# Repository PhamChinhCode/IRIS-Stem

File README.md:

# Bộ kit giảng dạy STEM – ESP32-S3 + MicroBlocks

Hệ thống module tái sử dụng để dạy nhà thông minh, robot và IoT cho học sinh 12–18 tuổi, lập trình kéo thả trên MicroBlocks.

## Đọc từ đâu

| Muốn biết | Mở |
|---|---|
| Kit gồm những gì, 25 dự án dùng module nào | [docs/THIET-KE-HE-THONG.md](docs/THIET-KE-HE-THONG.md) |
| Xem trực quan: dự án, sơ đồ nối dây, mô hình 3D, sơ đồ mạch | [stem-kit-map/index.html](stem-kit-map/index.html) |
| Sơ đồ nguyên lý, linh kiện, mạch in của từng bo | [hardware/THIET-KE-MACH.md](hardware/THIET-KE-MACH.md) |
| Chi tiết một bo tự thiết kế: gán chân, linh kiện, bố trí, kiểm thử | `hardware/<bo>/THIET-KE-<mã>.md`, ví dụ [THIET-KE-C1.md](hardware/C1-bo-chu/THIET-KE-C1.md) (có cho C1, C2, S1, S2, S3) |
| Kích thước bo, chi tiết in 3D, vỏ hộp, mô hình lắp ráp | [docs/THIET-KE-CO-KHI.md](docs/THIET-KE-CO-KHI.md) |
| Cách đưa tệp 3D, hình mạch, PDF lên trang web | [stem-kit-map/HUONG-DAN.md](stem-kit-map/HUONG-DAN.md) |

## Cấu trúc thư mục

```
docs/           Tài liệu thiết kế, hình minh hoạ
stem-kit-map/   Trang bản đồ kit (web) và lệnh cập nhật update_3d.py
hardware/       Mạch KiCad; THIET-KE-MACH.md là tài liệu thiết kế mạch
  common/         Thư viện ký hiệu, chân linh kiện, mã dựng sơ đồ và mạch in dùng chung
  C1-bo-chu/      Bo chủ ESP32-S3 (64 × 48 mm)
  C2-nguon-pin/   Nguồn pin 2S
  S1-driver-dong-co/
  S2-do-line/
  S3-imu/
  O7-servo-16-kenh/
  bo-mang/        19 bo mang cho module đơn giản (I1–I14, O1–O5), mỗi bo một thư mục
firmware/       Firmware STM32G030 của module thông minh
  common/         Khung I2C và bootloader dùng chung
  S1-driver-dong-co/
  S2-do-line/
  S3-imu/
libraries/      Thư viện khối MicroBlocks tự viết
mechanical/     Cơ khí: mã CAD tham số (src/), tệp in 3D (STL/)
projects/       Chương trình mẫu và mô hình lắp ráp của 25 dự án, theo 5 cấp độ
curriculum/     Giáo án, phiếu bài học
```

`Iris blocks/` là bản fork MicroBlocks (phần mềm lập trình và firmware máy ảo, giấy phép MPL 2.0). Các thay đổi so với bản gốc ghi trong [Iris blocks/DOC-STNAPP.md](Iris%20blocks/DOC-STNAPP.md); bối cảnh ở mục 12 của tài liệu thiết kế.

## Tình trạng

| Phần | Đã có | Còn thiếu |
|---|---|---|
| Sơ đồ nguyên lý | Đủ 25 bo, ERC không lỗi | Mã LCSC cho phần lớn linh kiện; đối chiếu datasheet HY2120-CB và 8205A trên C2 |
| Mạch in | 19 bo mang đã đi dây | C1, C2, S1, S2, S3, O7; soát tay và xuất Gerber cho 19 bo mang |
| Vỏ in 3D | Đế và nắp cho 19 bo mang (I3, I13 chỉ có đế) | Vỏ cho 6 bo còn lại |
| Mô hình lắp ráp | 7 cụm dự án, không va chạm; cánh tay robot dùng servo MG90S | Mô hình riêng cho từng dự án |
| Trang bản đồ kit | 25 dự án, 25 module, mô hình 3D, hình mạch, tài liệu PDF | |

## Trang bản đồ kit

Trang lấy dữ liệu thẳng từ các thư mục thiết kế. Sau khi sửa mạch hoặc mô hình, chạy một lệnh trong `stem-kit-map/`:

```bash
python update_3d.py
```

Lệnh tìm tệp theo **tên**, nên chỉ cần lưu đúng chỗ và đúng tên:

| Nội dung trên trang | Tệp nguồn | Ví dụ |
|---|---|---|
| Mô hình 3D của module | `hardware/**/<mã>.step` | `hardware/C1-bo-chu/C1.step` |
| Mô hình 3D của dự án | `projects/**/Project<số>.step` | `projects/Project11.step` |
| Sơ đồ nguyên lý | `hardware/**/<mã>.kicad_sch` | `hardware/bo-mang/I1/I1.kicad_sch` |
| Hình mạch in | `hardware/**/<mã>.kicad_pcb` | `hardware/bo-mang/I1/I1.kicad_pcb` |
| Tài liệu PDF | `hardware/**/<mã>.pdf` | `hardware/bo-mang/I1/I1.pdf` |

Module và dự án chưa có tệp riêng thì dùng mô hình dựng từ mã trong `mechanical/src`. Xuất hình mạch cần KiCad 10; đọc tệp STEP cần `cadgen` (xem hướng dẫn).

## Quy ước

- Mã module (C1, S1, I6, O3...) theo mục 4 của tài liệu thiết kế, dùng làm tiền tố tên thư mục và tên tệp.
- Mỗi module tự thiết kế có thư mục cùng tên ở `hardware/` và `firmware/`.
- Tệp trong `mechanical/STEP/` dựng lại được từ mã nên không đưa vào git. Riêng mô hình servo MG90S tải từ step.parts nằm ở `mechanical/STEP/mua_san/`, phải tải lại trên máy mới (tìm «Adafruit 1143» trên step.parts, lưu thành `adafruit_1143_micro_servo_high_torque_metal_gear.step`).
- Các lệnh sinh sơ đồ và mạch in (`ve_so_do.py`, `ve_pcb.py`) **ghi đè** tệp KiCad. Không chạy lại cho bo đã sửa tay.

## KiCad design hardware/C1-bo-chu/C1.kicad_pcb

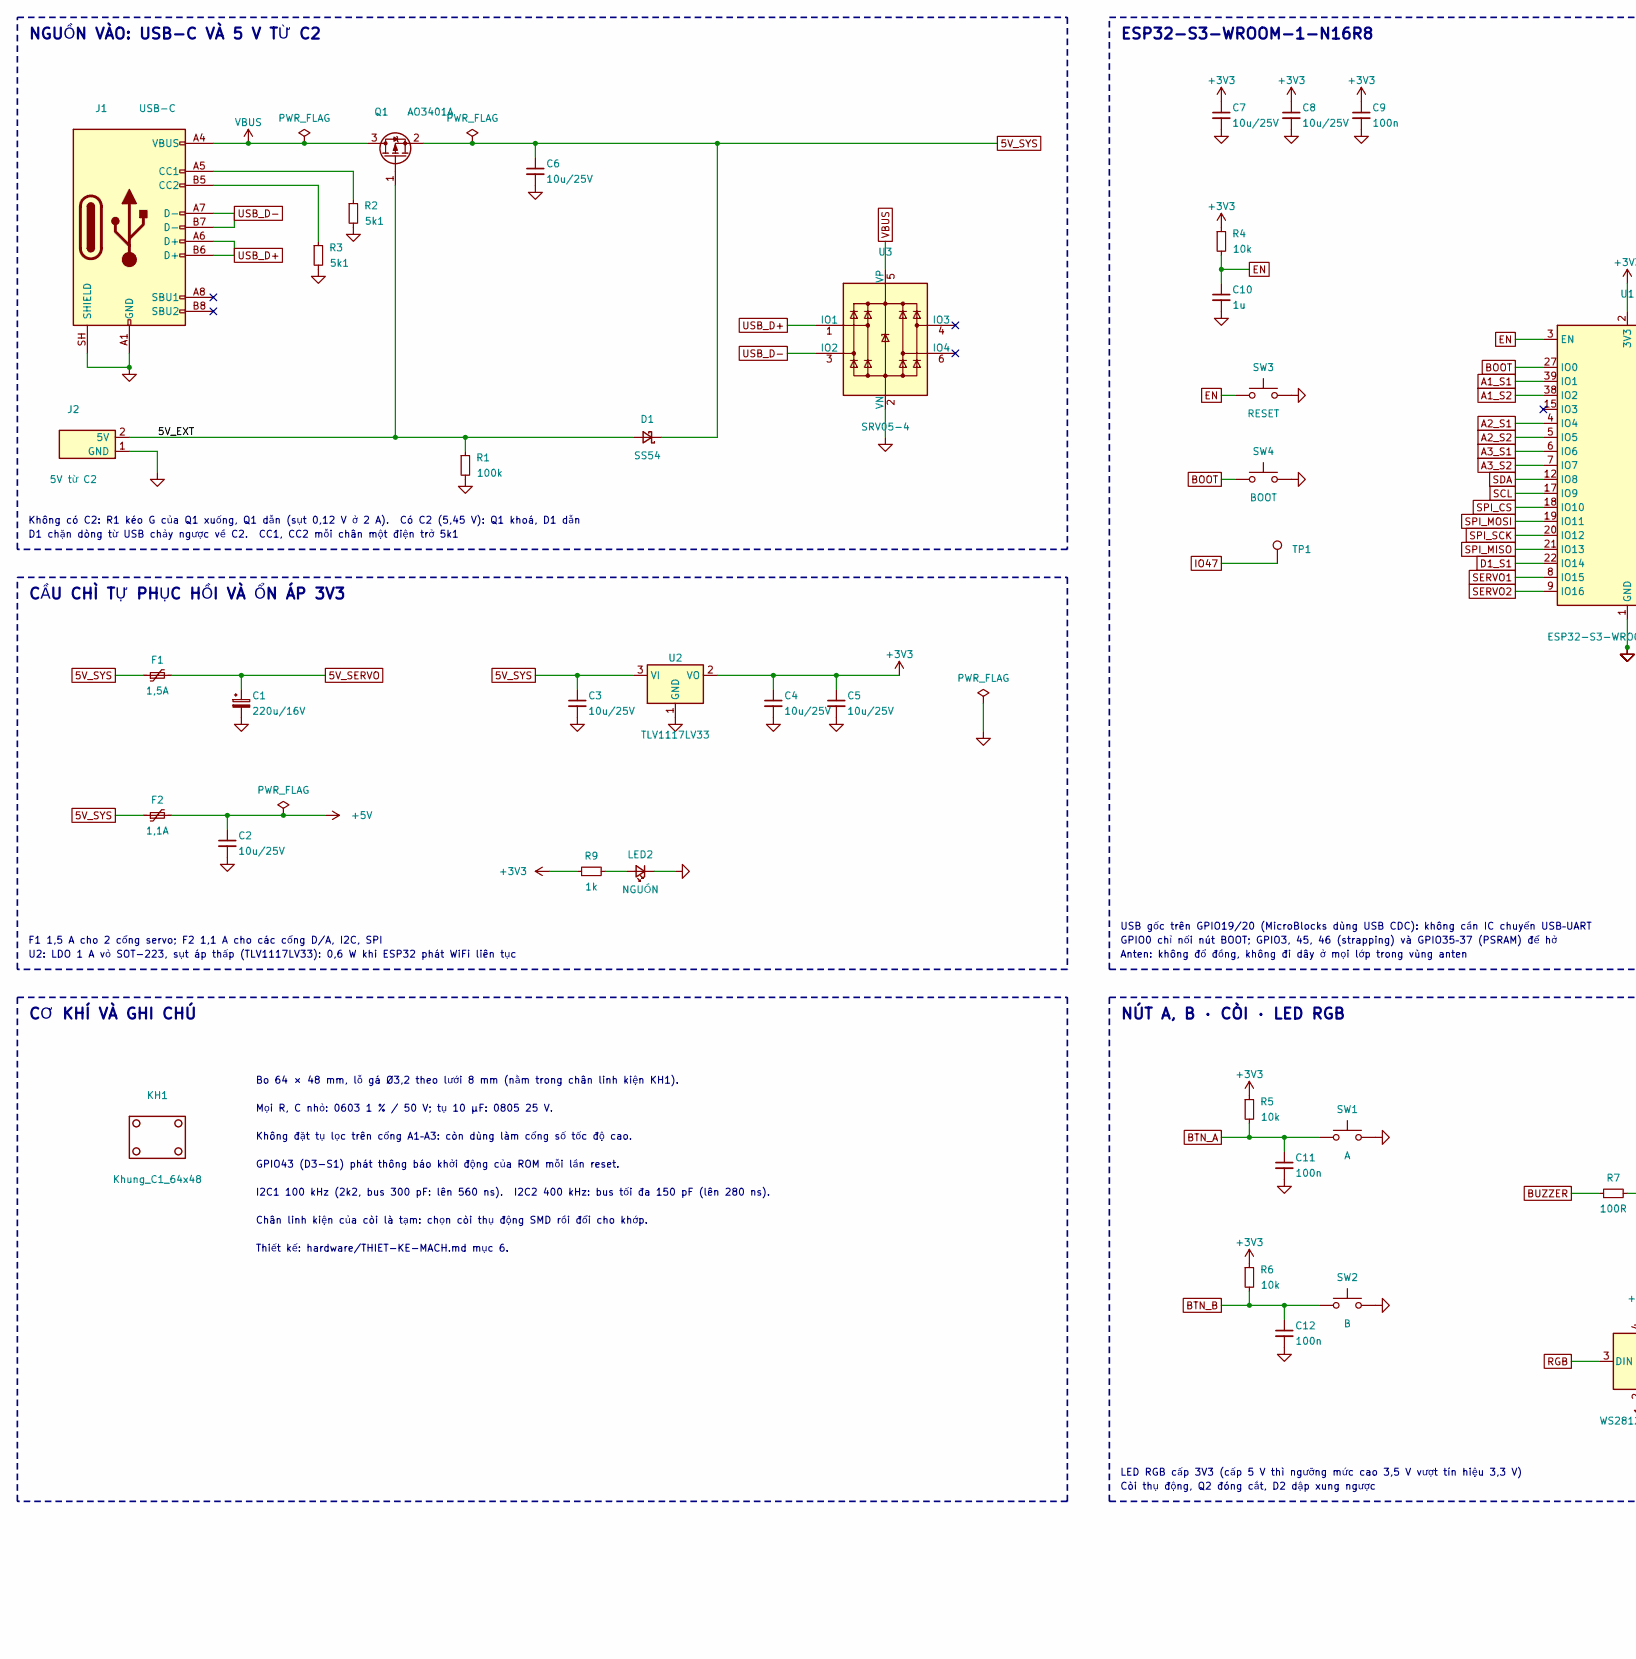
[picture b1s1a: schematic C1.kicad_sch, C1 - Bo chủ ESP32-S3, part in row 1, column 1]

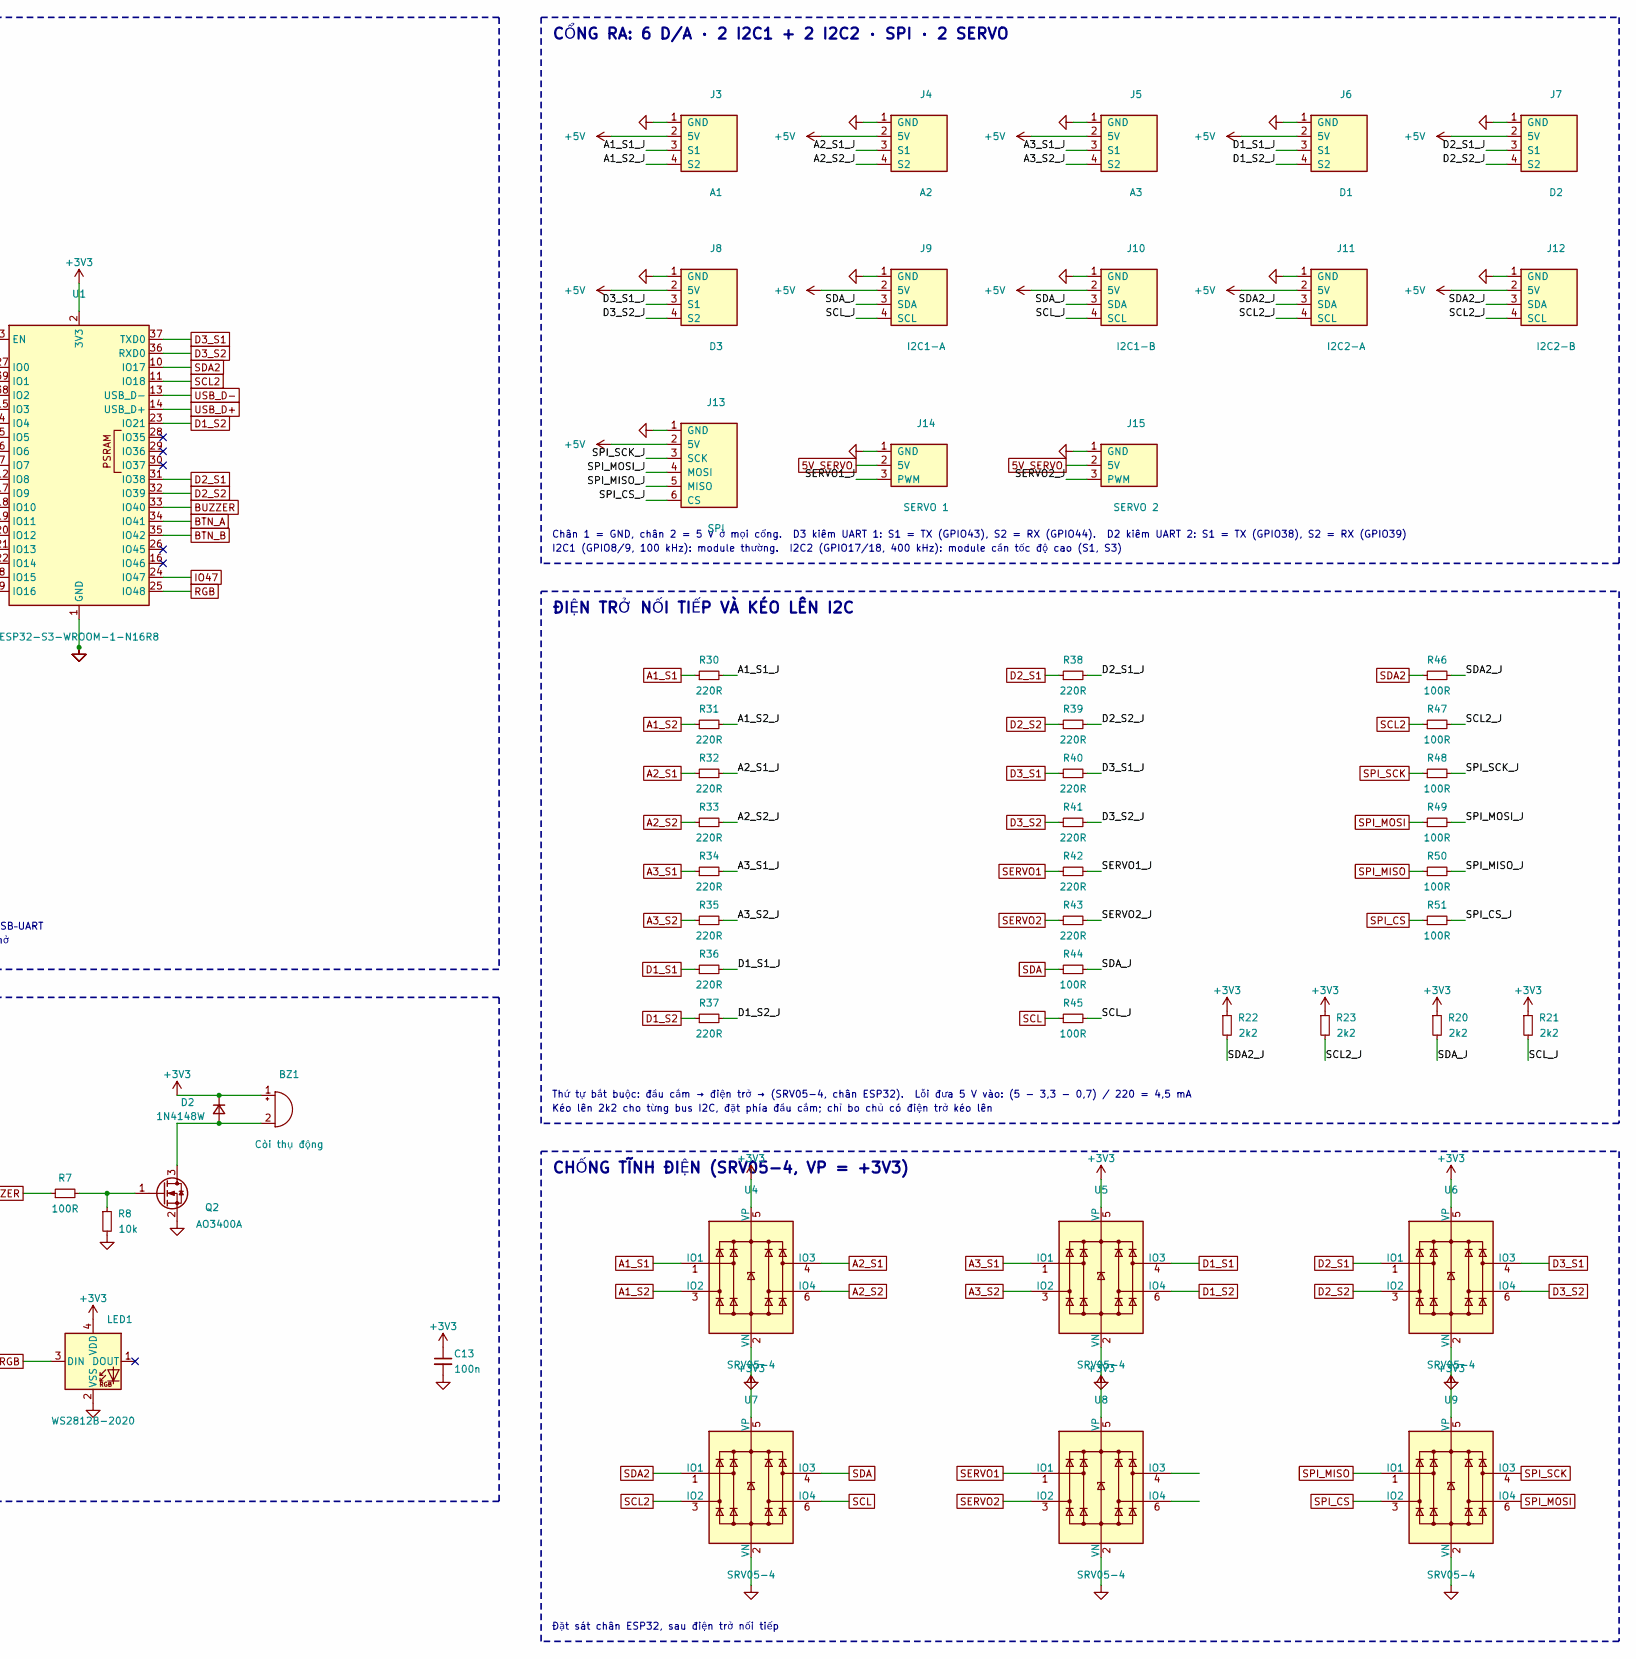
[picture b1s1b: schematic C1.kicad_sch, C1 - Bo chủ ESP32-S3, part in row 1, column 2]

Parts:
BZ1: Còi thụ động; Buzzer_Mallory_AST1109MLTRQ
C1: 220u/16V; CP_Radial_D6.3mm_P2.50mm
C2, C3, C4, C5, C6, C7, C8: 10u/25V; C_0805_2012Metric
C9, C11, C12, C13: 100n; C_0603_1608Metric
C10: 1u; C_0603_1608Metric
D1: SS54; D_SMA; MPN SS54
D2: 1N4148W; D_SOD-123; MPN 1N4148W
F1: 1,5A; Fuse_1210_3225Metric
F2: 1,1A; Fuse_1210_3225Metric
J1: USB-C; USB_C_Receptacle_HRO_TYPE-C-31-M-12; MPN TYPE-C-31-M-12
J2: 5V từ C2; JST_PH_B2B-PH-K_1x02_P2.00mm_Vertical
J3: A1; JST_PH_B4B-PH-K_1x04_P2.00mm_Vertical
J4: A2; JST_PH_B4B-PH-K_1x04_P2.00mm_Vertical
J5: A3; JST_PH_B4B-PH-K_1x04_P2.00mm_Vertical
J6: D1; JST_PH_B4B-PH-K_1x04_P2.00mm_Vertical
J7: D2; JST_PH_B4B-PH-K_1x04_P2.00mm_Vertical
J8: D3; JST_PH_B4B-PH-K_1x04_P2.00mm_Vertical
J9: I2C1-A; JST_PH_B4B-PH-K_1x04_P2.00mm_Vertical
J10: I2C1-B; JST_PH_B4B-PH-K_1x04_P2.00mm_Vertical
J11: I2C2-A; JST_PH_B4B-PH-K_1x04_P2.00mm_Vertical
J12: I2C2-B; JST_PH_B4B-PH-K_1x04_P2.00mm_Vertical
J13: SPI; JST_PH_B6B-PH-K_1x06_P2.00mm_Vertical
J14: SERVO 1; Cong_Servo_1x03
J15: SERVO 2; Cong_Servo_1x03
KH1: Khung_C1_64x48
LED1: WS2812B-2020; LED_WS2812B-2020_PLCC4_2.0x2.0mm; MPN WS2812B-2020
LED2: NGUỒN; LED_0603_1608Metric
Q1: AO3401A; SOT-23; MPN AO3401A
Q2: AO3400A; SOT-23; MPN AO3400A
R1: 100k; R_0603_1608Metric
R2, R3: 5k1; R_0603_1608Metric
R4, R5, R6, R8: 10k; R_0603_1608Metric
R7, R44, R45, R46, R47, R48, R49, R50, R51: 100R; R_0603_1608Metric
R9: 1k; R_0603_1608Metric
R20, R21, R22, R23: 2k2; R_0603_1608Metric
R30, R31, R32, R33, R34, R35, R36, R37, R38, R39, R40, R41, R42, R43: 220R; R_0603_1608Metric
SW1: A; SW_Push_1P1T_NO_E-Switch_TL3301NxxxxxG
SW2: B; SW_Push_1P1T_NO_E-Switch_TL3301NxxxxxG
SW3: RESET; SW_SPST_TS-1088-xR025
SW4: BOOT; SW_SPST_TS-1088-xR025
TP1: IO47; TestPoint_Pad_D1.5mm
U1: ESP32-S3-WROOM-1-N16R8; ESP32-S3-WROOM-1; MPN ESP32-S3-WROOM-1-N16R8; LCSC C2913202
U2: TLV1117LV33; SOT-223-3_TabPin2; MPN TLV1117LV33DCYR
U3, U4, U5, U6, U7, U8, U9: SRV05-4; SOT-23-6; MPN SRV05-4

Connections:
5V_SERVO: C1.1, F1.2, J14.2 (5V), J15.2 (5V)
5V_SYS: C3.1, C6.1, D1.1 (K), F1.1, F2.1, Q1.2 (S), U2.3 (VI)
+3V3: BZ1.1 (+), C4.1, C5.1, C7.1, C8.1, C9.1, C13.1, D2.1 (K), LED1.4 (VDD), R4.1, R5.1, R6.1, R9.1, R20.1, R21.1, R22.1, R23.1, U1.2 (3V3), U2.2 (VO), U4.5 (VP), U5.5 (VP), U6.5 (VP), U7.5 (VP), U8.5 (VP), U9.5 (VP)
+5V: C2.1, F2.2, J3.2 (5V), J4.2 (5V), J5.2 (5V), J6.2 (5V), J7.2 (5V), J8.2 (5V), J9.2 (5V), J10.2 (5V), J11.2 (5V), J12.2 (5V), J13.2 (5V)
/5V_EXT: D1.2 (A), J2.2 (5V), Q1.1 (G), R1.1
/A1_S1_J: J3.3 (S1), R30.2
/A1_S2_J: J3.4 (S2), R31.2
/A2_S1_J: J4.3 (S1), R32.2
/A2_S2_J: J4.4 (S2), R33.2
/A3_S1_J: J5.3 (S1), R34.2
/A3_S2_J: J5.4 (S2), R35.2
/D1_S1_J: J6.3 (S1), R36.2
/D1_S2_J: J6.4 (S2), R37.2
/D2_S1_J: J7.3 (S1), R38.2
/D2_S2_J: J7.4 (S2), R39.2
/D3_S1_J: J8.3 (S1), R40.2
/D3_S2_J: J8.4 (S2), R41.2
/SCL2_J: J11.4 (SCL), J12.4 (SCL), R23.2, R47.2
/SCL_J: J9.4 (SCL), J10.4 (SCL), R21.2, R45.2
/SDA2_J: J11.3 (SDA), J12.3 (SDA), R22.2, R46.2
/SDA_J: J9.3 (SDA), J10.3 (SDA), R20.2, R44.2
/SERVO1_J: J14.3 (PWM), R42.2
/SERVO2_J: J15.3 (PWM), R43.2
/SPI_CS_J: J13.6 (CS), R51.2
/SPI_MISO_J: J13.5 (MISO), R50.2
/SPI_MOSI_J: J13.4 (MOSI), R49.2
/SPI_SCK_J: J13.3 (SCK), R48.2
A1_S1: R30.1, U1.39 (IO1), U4.1 (IO1)
A1_S2: R31.1, U1.38 (IO2), U4.3 (IO2)
A2_S1: R32.1, U1.4 (IO4), U4.4 (IO3)
A2_S2: R33.1, U1.5 (IO5), U4.6 (IO4)
A3_S1: R34.1, U1.6 (IO6), U5.1 (IO1)
A3_S2: R35.1, U1.7 (IO7), U5.3 (IO2)
BOOT: SW4.1, U1.27 (IO0)
BTN_A: C11.1, R5.2, SW1.1, U1.34 (IO41)
BTN_B: C12.1, R6.2, SW2.1, U1.35 (IO42)
BUZZER: R7.1, U1.33 (IO40)
D1_S1: R36.1, U1.22 (IO14), U5.4 (IO3)
D1_S2: R37.1, U1.23 (IO21), U5.6 (IO4)
D2_S1: R38.1, U1.31 (IO38), U6.1 (IO1)
D2_S2: R39.1, U1.32 (IO39), U6.3 (IO2)
D3_S1: R40.1, U1.37 (TXD0), U6.4 (IO3)
D3_S2: R41.1, U1.36 (RXD0), U6.6 (IO4)
EN: C10.1, R4.2, SW3.1, U1.3 (EN)
GND: C1.2, C2.2, C3.2, C4.2, C5.2, C6.2, C7.2, C8.2, C9.2, C10.2, C11.2, C12.2, C13.2, J1.A1 (GND), J1.A12 (GND), J1.B1 (GND), J1.B12 (GND), J1.SH (SHIELD), J2.1 (GND), J3.1 (GND), J4.1 (GND), J5.1 (GND), J6.1 (GND), J7.1 (GND), J8.1 (GND), J9.1 (GND), J10.1 (GND), J11.1 (GND), J12.1 (GND), J13.1 (GND), J14.1 (GND), J15.1 (GND), LED1.2 (VSS), LED2.1 (K), Q2.2 (S), R1.2, R2.2, R3.2, R8.2, SW1.2, SW2.2, SW3.2, SW4.2, U1.1 (GND), U1.40 (GND), U1.41 (GND), U2.1 (GND), U3.2 (VN), U4.2 (VN), U5.2 (VN), U6.2 (VN), U7.2 (VN), U8.2 (VN), U9.2 (VN)
IO47: TP1.1 (1_1), U1.24 (IO47)
unnamed: BZ1.2 (-), D2.2 (A), Q2.3 (D)
unnamed: J1.A5 (CC1), R2.1
unnamed: J1.B5 (CC2), R3.1
unnamed: LED2.2 (A), R9.2
unnamed: Q2.1 (G), R7.2, R8.1
RGB: LED1.3 (DIN), U1.25 (IO48)
SCL: R45.1, U1.17 (IO9), U7.6 (IO4)
SCL2: R47.1, U1.11 (IO18), U7.3 (IO2)
SDA: R44.1, U1.12 (IO8), U7.4 (IO3)
SDA2: R46.1, U1.10 (IO17), U7.1 (IO1)
SERVO1: R42.1, U1.8 (IO15), U8.1 (IO1)
SERVO2: R43.1, U1.9 (IO16), U8.3 (IO2)
SPI_CS: R51.1, U1.18 (IO10), U9.3 (IO2)
SPI_MISO: R50.1, U1.21 (IO13), U9.1 (IO1)
SPI_MOSI: R49.1, U1.19 (IO11), U9.6 (IO4)
SPI_SCK: R48.1, U1.20 (IO12), U9.4 (IO3)
USB_D+: J1.A6 (D+), J1.B6 (D+), U1.14 (USB_D+), U3.1 (IO1)
USB_D-: J1.A7 (D-), J1.B7 (D-), U1.13 (USB_D-), U3.3 (IO2)
VBUS: J1.A4 (VBUS), J1.A9 (VBUS), J1.B4 (VBUS), J1.B9 (VBUS), Q1.3 (D), U3.5 (VP)

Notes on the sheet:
NÚT A, B · CÒI · LED RGB
F1 1,5 A cho 2 cổng servo; F2 1,1 A cho các cổng D/A, I2C, SPI
Không đặt tụ lọc trên cổng A1–A3: còn dùng làm cổng số tốc độ cao.
NGUỒN VÀO: USB-C VÀ 5 V TỪ C2
ĐIỆN TRỞ NỐI TIẾP VÀ KÉO LÊN I2C
I2C1 100 kHz (2k2, bus 300 pF: lên 560 ns). I2C2 400 kHz: bus tối đa 150 pF (lên 280 ns).
Không có C2: R1 kéo G của Q1 xuống, Q1 dẫn (sụt 0,12 V ở 2 A). Có C2 (5,45 V): Q1 khoá, D1 dẫn
Thứ tự bắt buộc: đầu cắm → điện trở → (SRV05-4, chân ESP32). Lỗi đưa 5 V vào: (5 − 3,3 − 0,7) / 220 = 4,5 mA
ESP32-S3-WROOM-1-N16R8
Anten: không đổ đồng, không đi dây ở mọi lớp trong vùng anten
Bo 64 × 48 mm, lỗ gá Ø3,2 theo lưới 8 mm (nằm trong chân linh kiện KH1).
Mọi R, C nhỏ: 0603 1 % / 50 V; tụ 10 µF: 0805 25 V.
Kéo lên 2k2 cho từng bus I2C, đặt phía đầu cắm; chỉ bo chủ có điện trở kéo lên
Đặt sát chân ESP32, sau điện trở nối tiếp
USB gốc trên GPIO19/20 (MicroBlocks dùng USB CDC): không cần IC chuyển USB–UART
I2C1 (GPIO8/9, 100 kHz): module thường. I2C2 (GPIO17/18, 400 kHz): module cần tốc độ cao (S1, S3)
GPIO43 (D3-S1) phát thông báo khởi động của ROM mỗi lần reset.
CƠ KHÍ VÀ GHI CHÚ
D1 chặn dòng từ USB chảy ngược về C2. CC1, CC2 mỗi chân một điện trở 5k1
U2: LDO 1 A vỏ SOT-223, sụt áp thấp (TLV1117LV33): 0,6 W khi ESP32 phát WiFi liên tục
LED RGB cấp 3V3 (cấp 5 V thì ngưỡng mức cao 3,5 V vượt tín hiệu 3,3 V)
CHỐNG TĨNH ĐIỆN (SRV05-4, VP = +3V3)
CỔNG RA: 6 D/A · 2 I2C1 + 2 I2C2 · SPI · 2 SERVO
Còi thụ động, Q2 đóng cắt, D2 dập xung ngược
GPIO0 chỉ nối nút BOOT; GPIO3, 45, 46 (strapping) và GPIO35–37 (PSRAM) để hở
Chân linh kiện của còi là tạm: chọn còi thụ động SMD rồi đổi cho khớp.
CẦU CHÌ TỰ PHỤC HỒI VÀ ỔN ÁP 3V3
Thiết kế: hardware/THIET-KE-MACH.md mục 6.
Chân 1 = GND, chân 2 = 5 V ở mọi cổng. D3 kiêm UART 1: S1 = TX (GPIO43), S2 = RX (GPIO44). D2 kiêm UART 2: S1 = TX (GPIO38), S2 = RX (GPIO39)

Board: 2 copper layers, 87 parts (0 on the bottom side), 65 nets, no tracks yet.

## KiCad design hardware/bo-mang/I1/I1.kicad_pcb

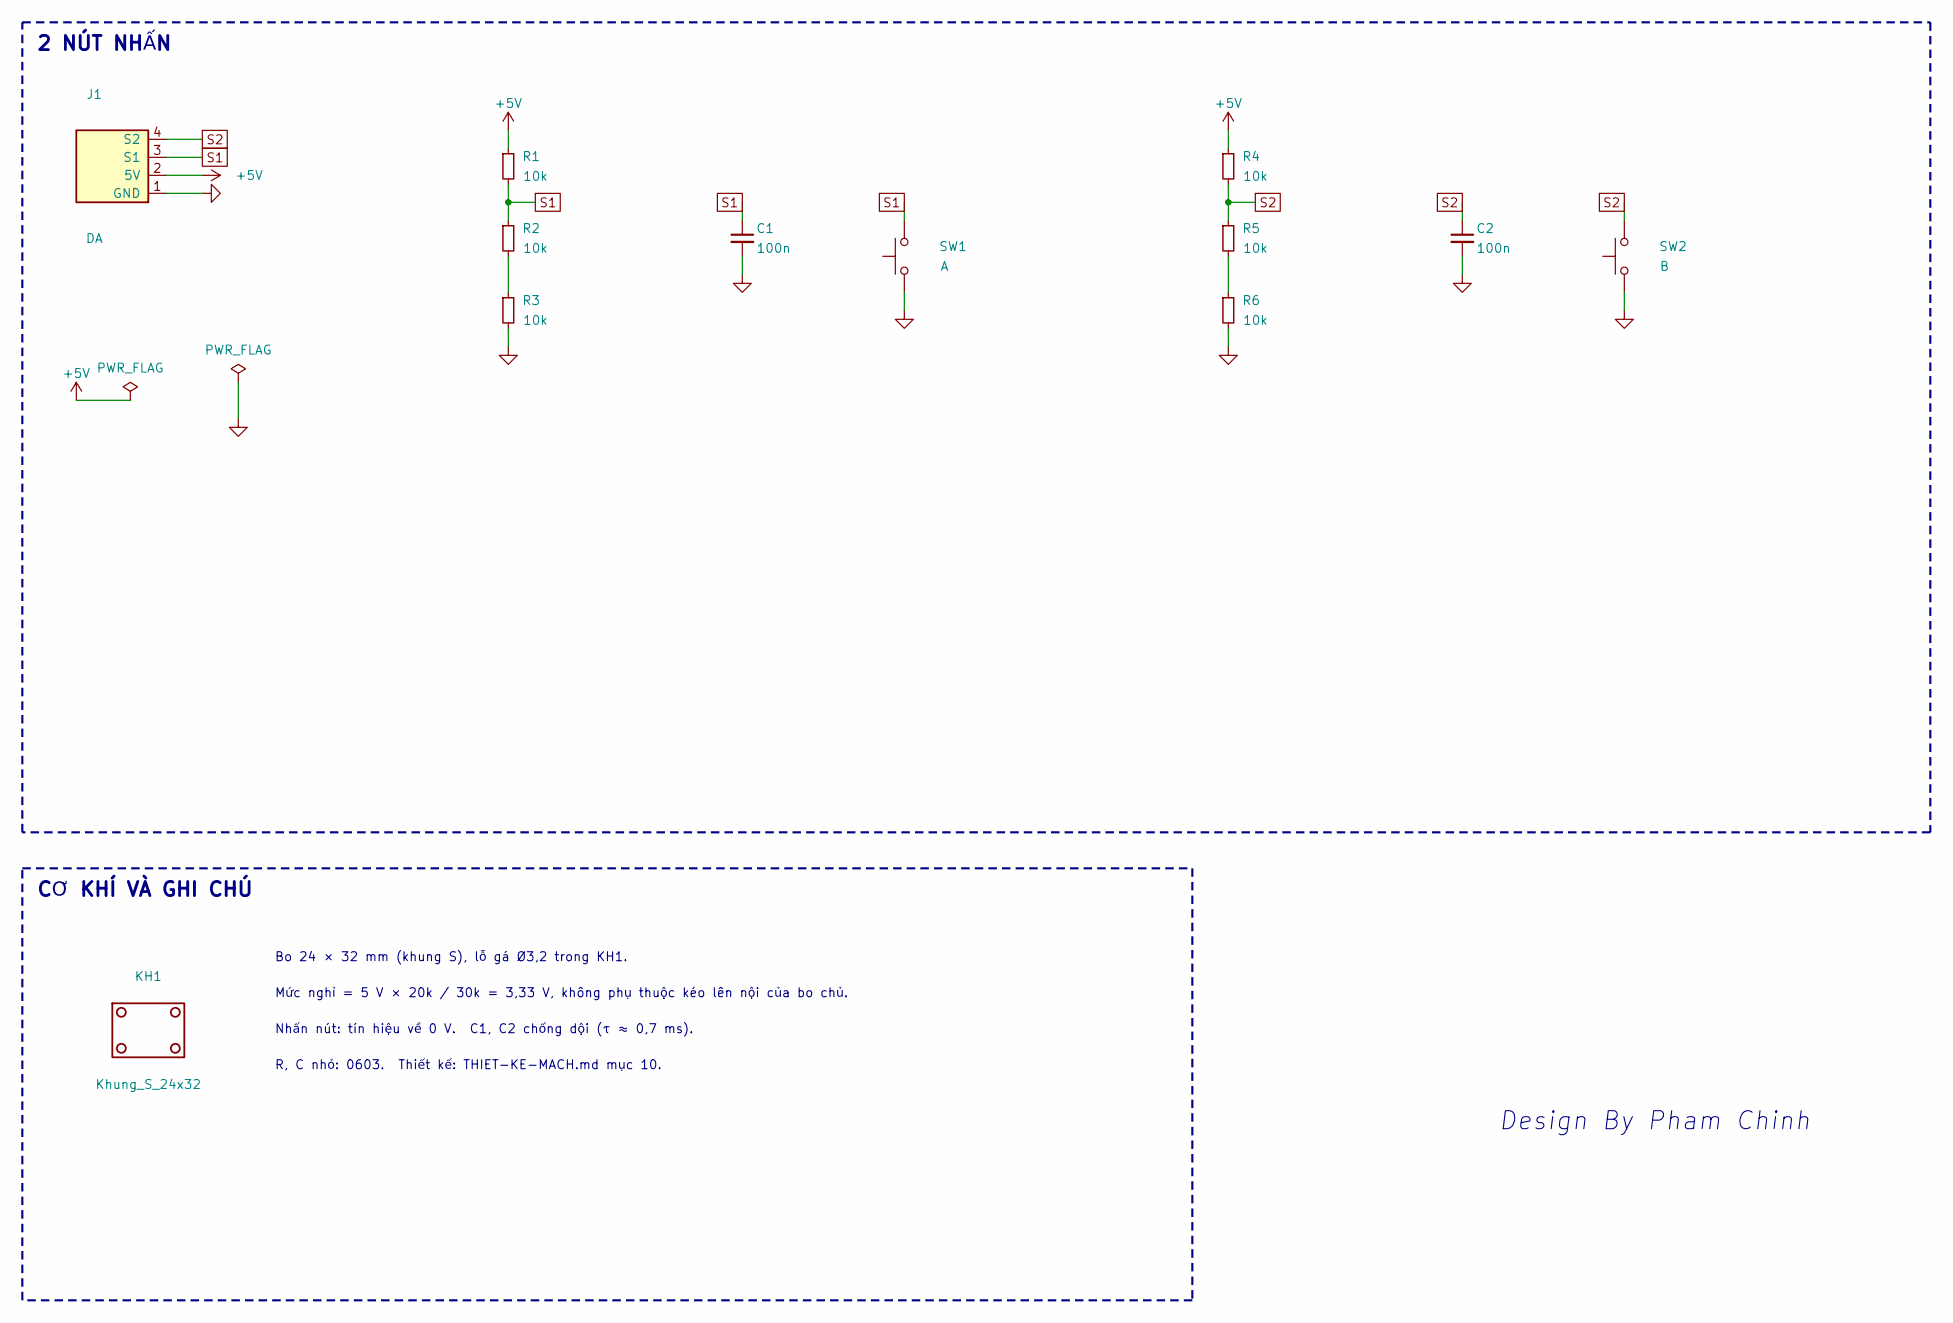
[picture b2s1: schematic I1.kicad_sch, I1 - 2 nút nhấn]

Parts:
C1, C2: 100n; C_0603_1608Metric
J1: DA; Cong_PH_4P_Ngang
KH1: Khung_S_24x32
R1, R2, R3, R4, R5, R6: 10k; R_0603_1608Metric
SW1: A; SW_Push_1TS009xxxx-xxxx-xxxx_6x6x5mm
SW2: B; SW_Push_1TS009xxxx-xxxx-xxxx_6x6x5mm

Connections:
+5V: J1.2 (5V), R1.1, R4.1
GND: C1.2, C2.2, J1.1 (GND), R3.2, R6.2, SW1.1, SW2.1
unnamed: R2.2, R3.1
unnamed: R5.2, R6.1
S1: C1.1, J1.3 (S1), R1.2, R2.1, SW1.2
S2: C2.1, J1.4 (S2), R4.2, R5.1, SW2.2

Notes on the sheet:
R, C nhỏ: 0603. Thiết kế: THIET-KE-MACH.md mục 10.
Nhấn nút: tín hiệu về 0 V. C1, C2 chống dội (τ ≈ 0,7 ms).
Mức nghỉ = 5 V × 20k / 30k = 3,33 V, không phụ thuộc kéo lên nội của bo chủ.
2 NÚT NHẤN
Bo 24 × 32 mm (khung S), lỗ gá Ø3,2 trong KH1.
Design By Pham Chinh
CƠ KHÍ VÀ GHI CHÚ

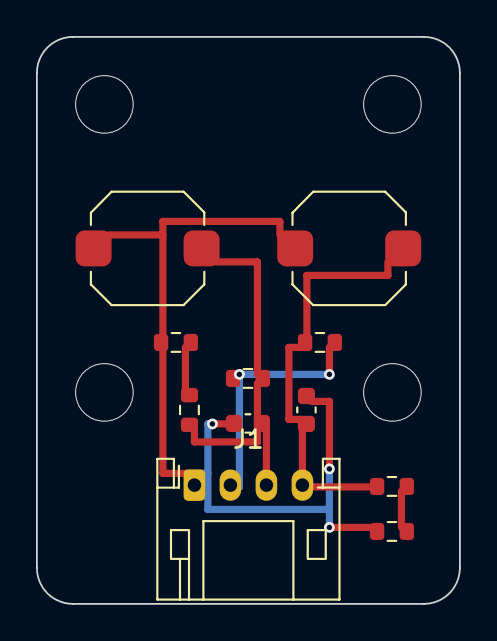
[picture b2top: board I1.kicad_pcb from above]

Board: 2 copper layers, 23.5 x 31.5 mm, 12 parts (0 on the bottom side), 6 nets.

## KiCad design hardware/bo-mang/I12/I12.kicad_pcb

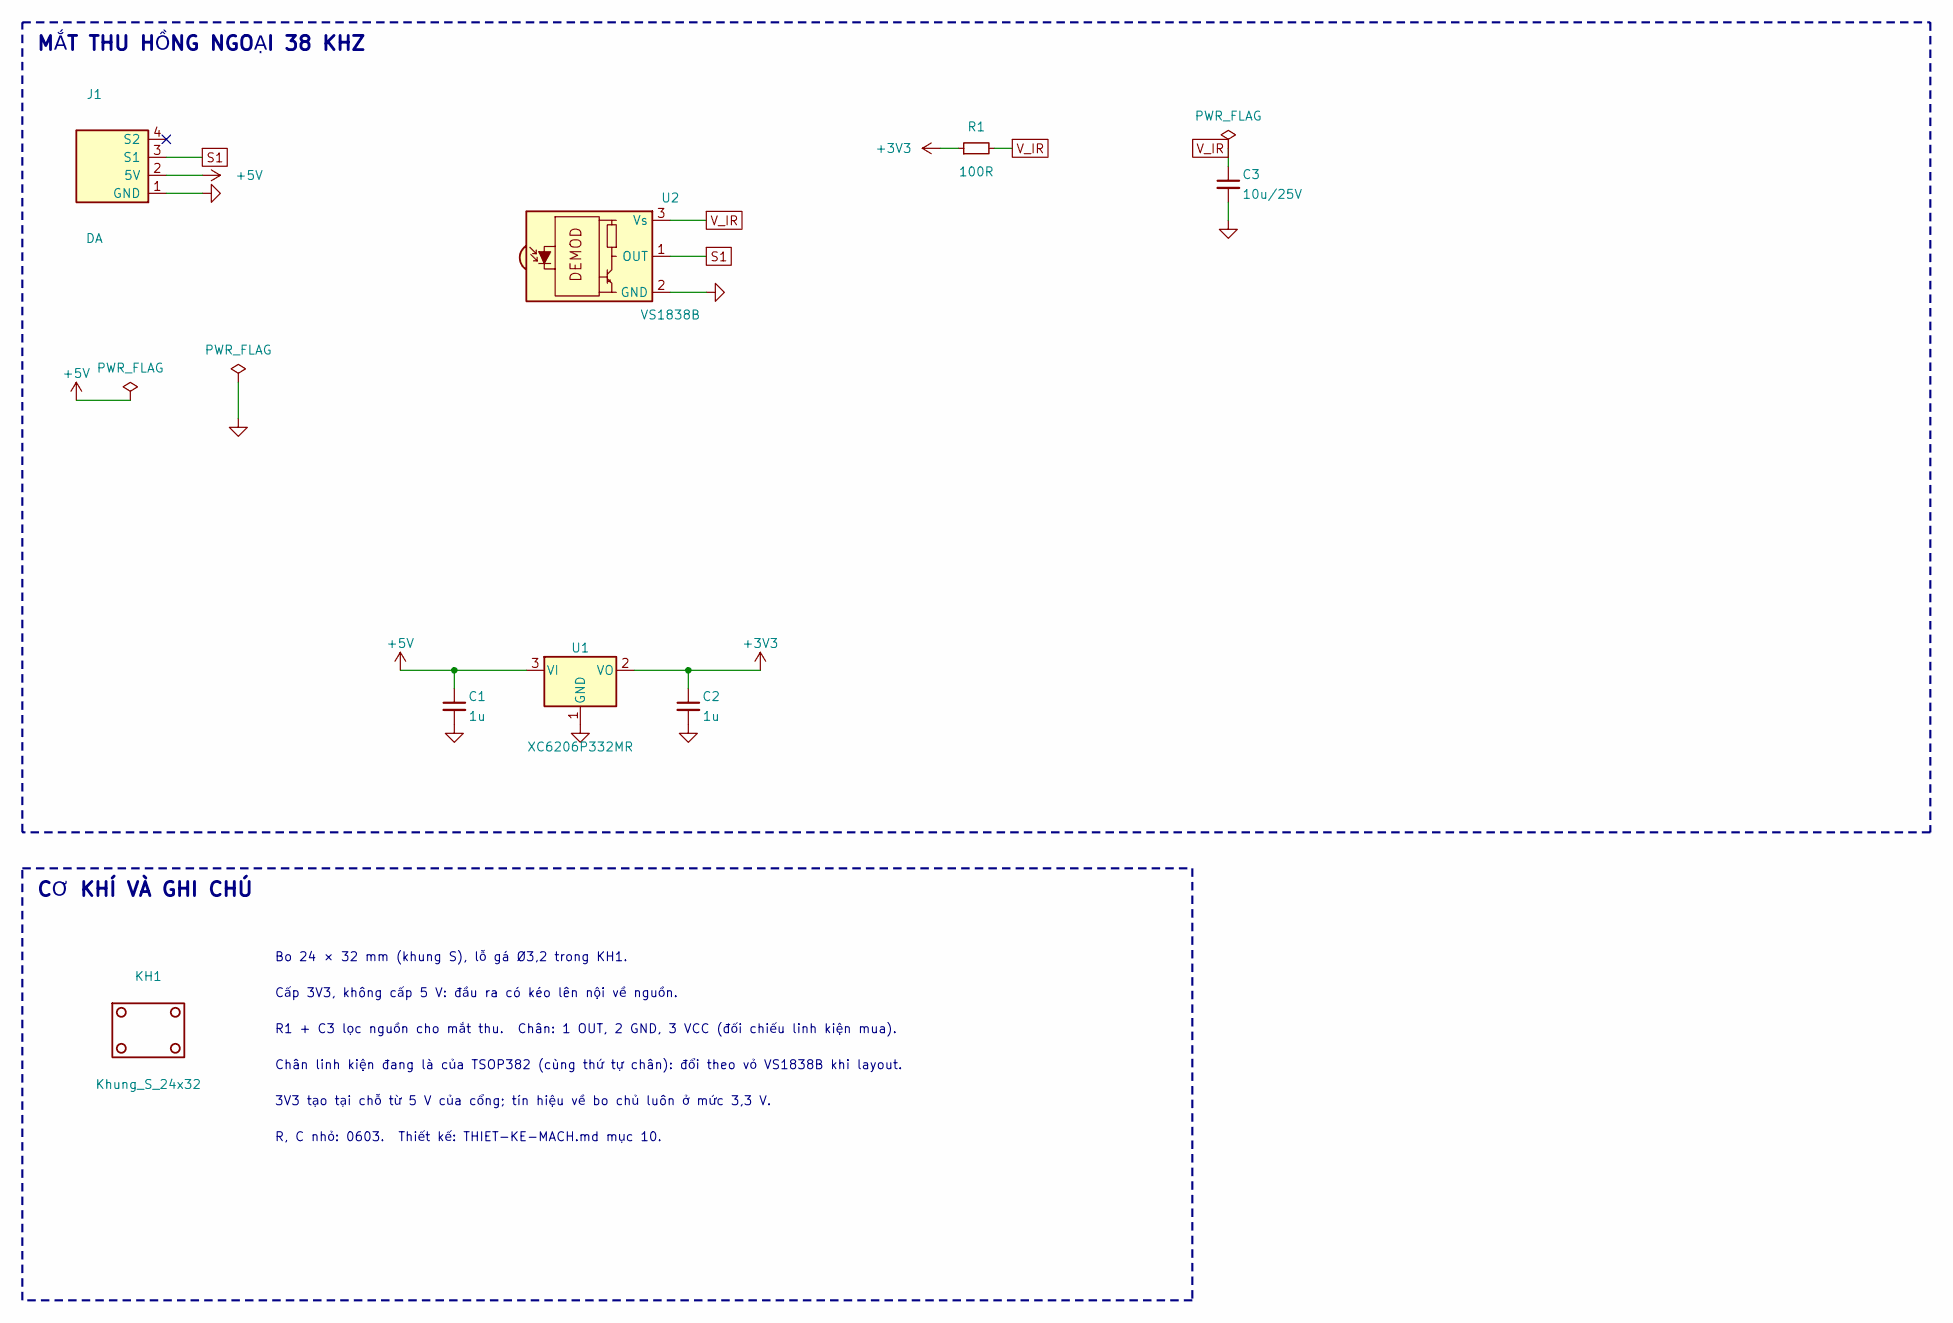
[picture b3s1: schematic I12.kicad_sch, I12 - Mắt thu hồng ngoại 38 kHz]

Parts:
C1, C2: 1u; C_0603_1608Metric
C3: 10u/25V; C_0805_2012Metric
J1: DA; Cong_PH_4P_Ngang
KH1: Khung_S_24x32
R1: 100R; R_0603_1608Metric
U1: XC6206P332MR; SOT-23-3; MPN XC6206P332MR
U2: VS1838B; Vishay_MINICAST-3Pin; MPN VS1838B

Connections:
+3V3: C2.1, R1.1, U1.2 (VO)
+5V: C1.1, J1.2 (5V), U1.3 (VI)
GND: C1.2, C2.2, C3.2, J1.1 (GND), U1.1 (GND), U2.2 (GND)
S1: J1.3 (S1), U2.1 (OUT)
V_IR: C3.1, R1.2, U2.3 (Vs)

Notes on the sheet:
MẮT THU HỒNG NGOẠI 38 KHZ
CƠ KHÍ VÀ GHI CHÚ
Bo 24 × 32 mm (khung S), lỗ gá Ø3,2 trong KH1.
Cấp 3V3, không cấp 5 V: đầu ra có kéo lên nội về nguồn.
R1 + C3 lọc nguồn cho mắt thu. Chân: 1 OUT, 2 GND, 3 VCC (đối chiếu linh kiện mua).
Chân linh kiện đang là của TSOP382 (cùng thứ tự chân): đổi theo vỏ VS1838B khi layout.
3V3 tạo tại chỗ từ 5 V của cổng; tín hiệu về bo chủ luôn ở mức 3,3 V.
R, C nhỏ: 0603. Thiết kế: THIET-KE-MACH.md mục 10.

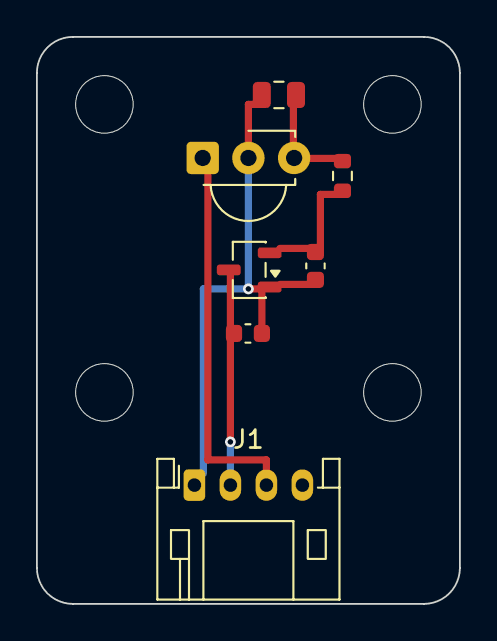
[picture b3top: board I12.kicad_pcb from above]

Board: 2 copper layers, 23.5 x 31.5 mm, 8 parts (0 on the bottom side), 5 nets.

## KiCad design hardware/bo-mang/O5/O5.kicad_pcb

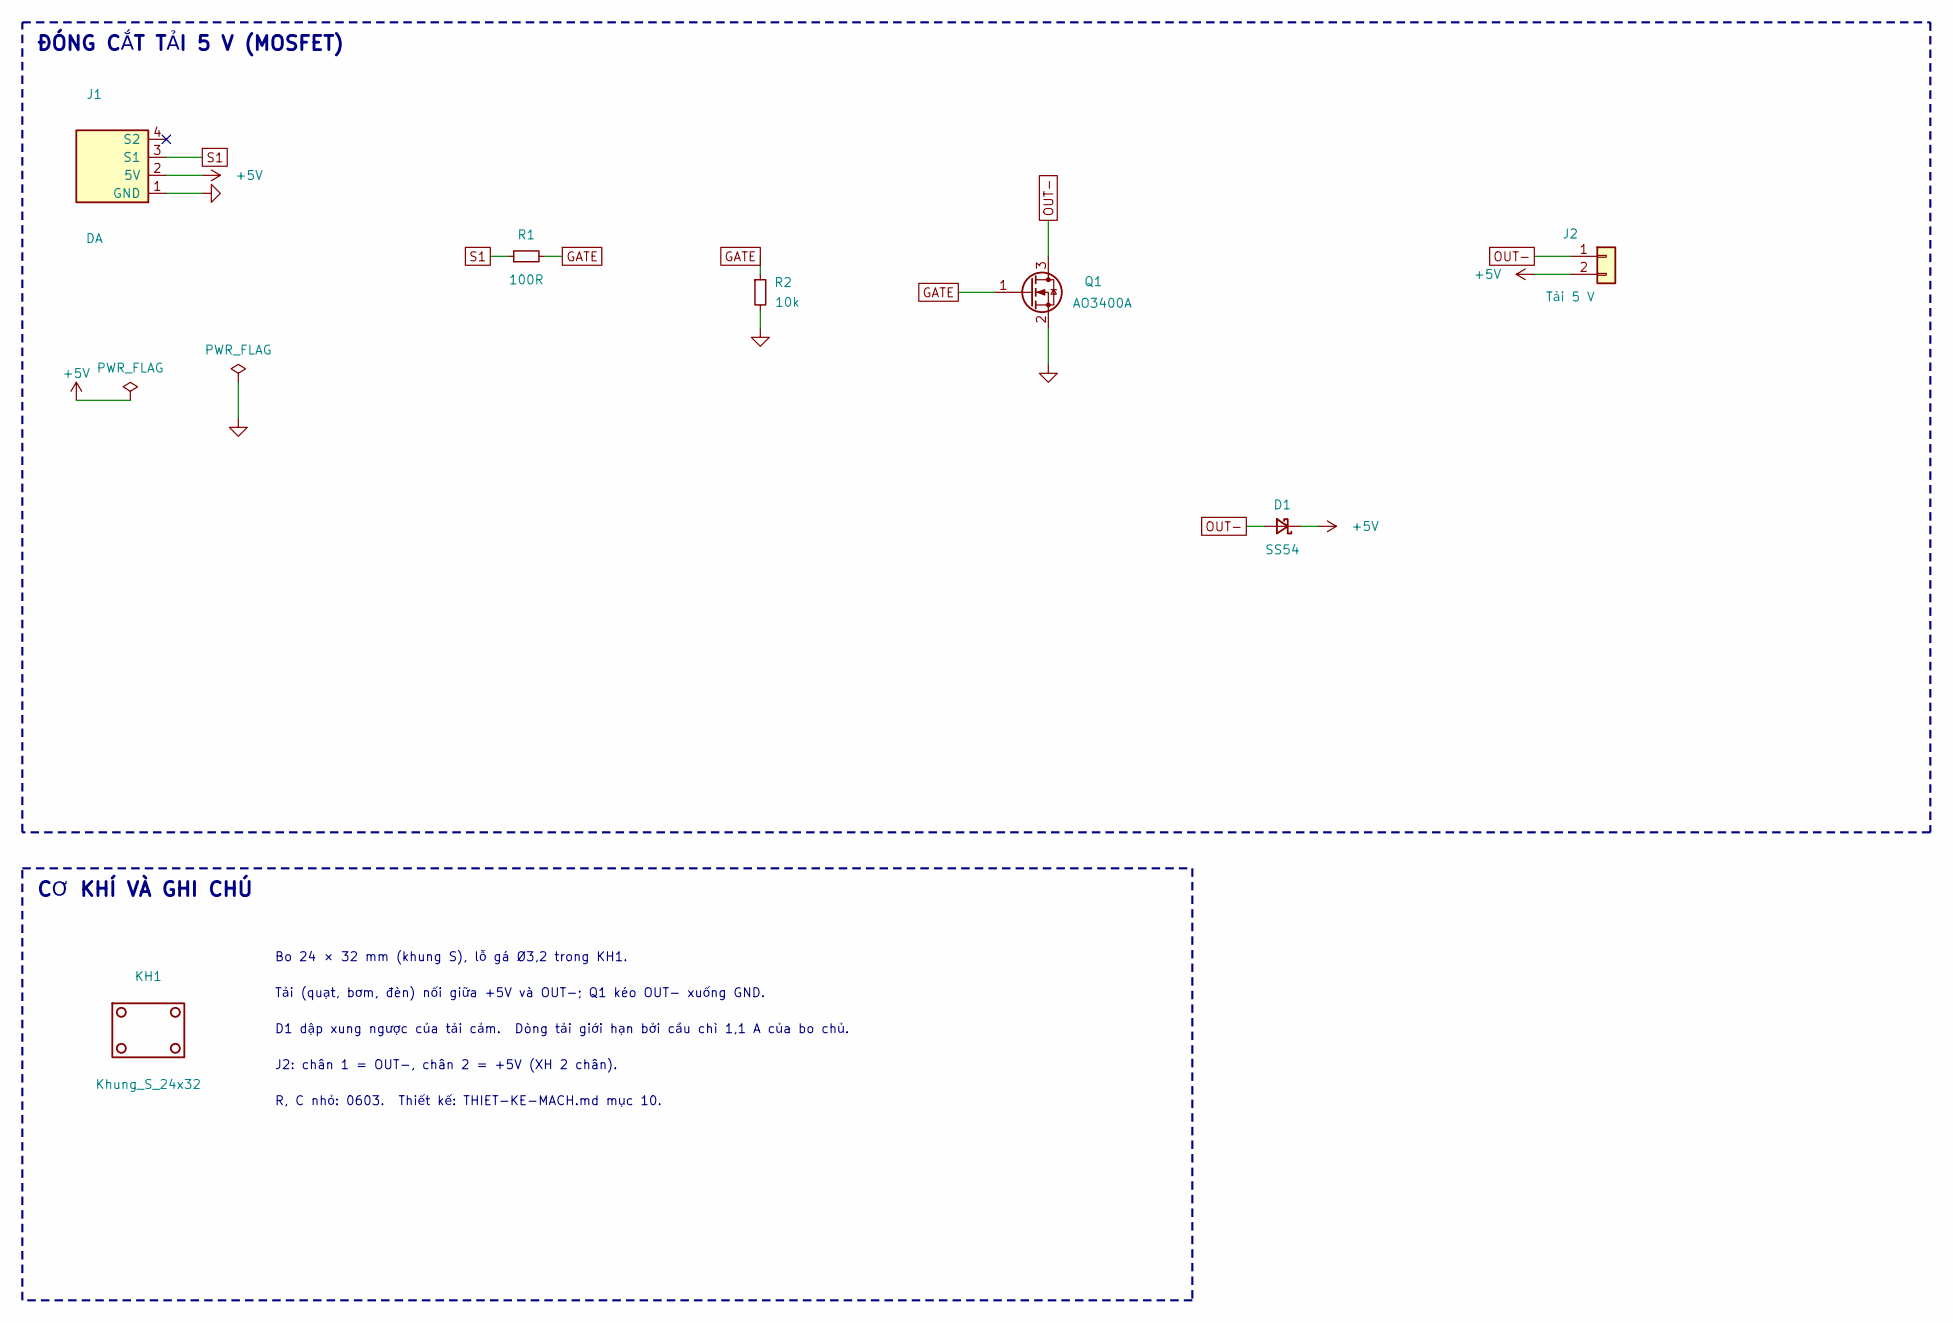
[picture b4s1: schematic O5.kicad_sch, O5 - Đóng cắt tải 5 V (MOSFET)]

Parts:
D1: SS54; D_SMA
J1: DA; Cong_PH_4P_Ngang
J2: Tải 5 V; Cong_XH_2P_Ngang
KH1: Khung_S_24x32
Q1: AO3400A; SOT-23; MPN AO3400A
R1: 100R; R_0603_1608Metric
R2: 10k; R_0603_1608Metric

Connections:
+5V: D1.1 (K), J1.2 (5V), J2.2
GATE: Q1.1 (G), R1.2, R2.1
GND: J1.1 (GND), Q1.2 (S), R2.2
OUT-: D1.2 (A), J2.1, Q1.3 (D)
S1: J1.3 (S1), R1.1

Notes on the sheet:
ĐÓNG CẮT TẢI 5 V (MOSFET)
CƠ KHÍ VÀ GHI CHÚ
Bo 24 × 32 mm (khung S), lỗ gá Ø3,2 trong KH1.
Tải (quạt, bơm, đèn) nối giữa +5V và OUT−; Q1 kéo OUT− xuống GND.
D1 dập xung ngược của tải cảm. Dòng tải giới hạn bởi cầu chì 1,1 A của bo chủ.
J2: chân 1 = OUT−, chân 2 = +5V (XH 2 chân).
R, C nhỏ: 0603. Thiết kế: THIET-KE-MACH.md mục 10.

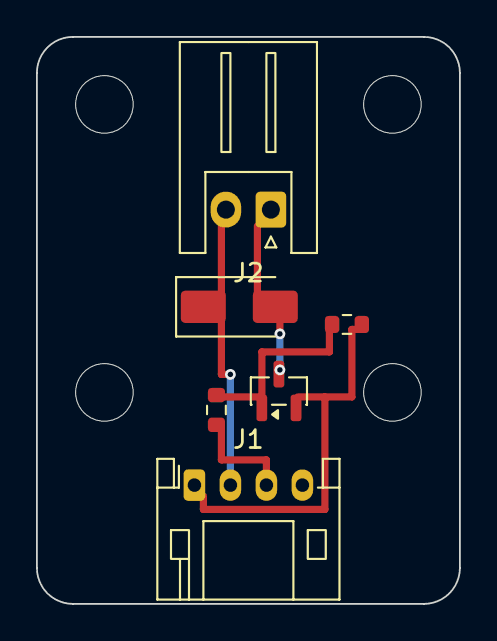
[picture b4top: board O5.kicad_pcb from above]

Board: 2 copper layers, 23.5 x 31.5 mm, 7 parts (0 on the bottom side), 5 nets.
